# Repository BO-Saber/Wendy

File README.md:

# Wendy
---
I build a powerful WiFi Analyzer Toolkit using Wemos D1 Mini (ESP8266) to scan nearby networks, This DIY project is perfect for Arduino lovers, robotics enthusiasts, and anyone interested in network tools and wireless optimization.

---
# Design

# Circuit Diagram 

# quartzcomponents.com Cart

# Zbotic Cart

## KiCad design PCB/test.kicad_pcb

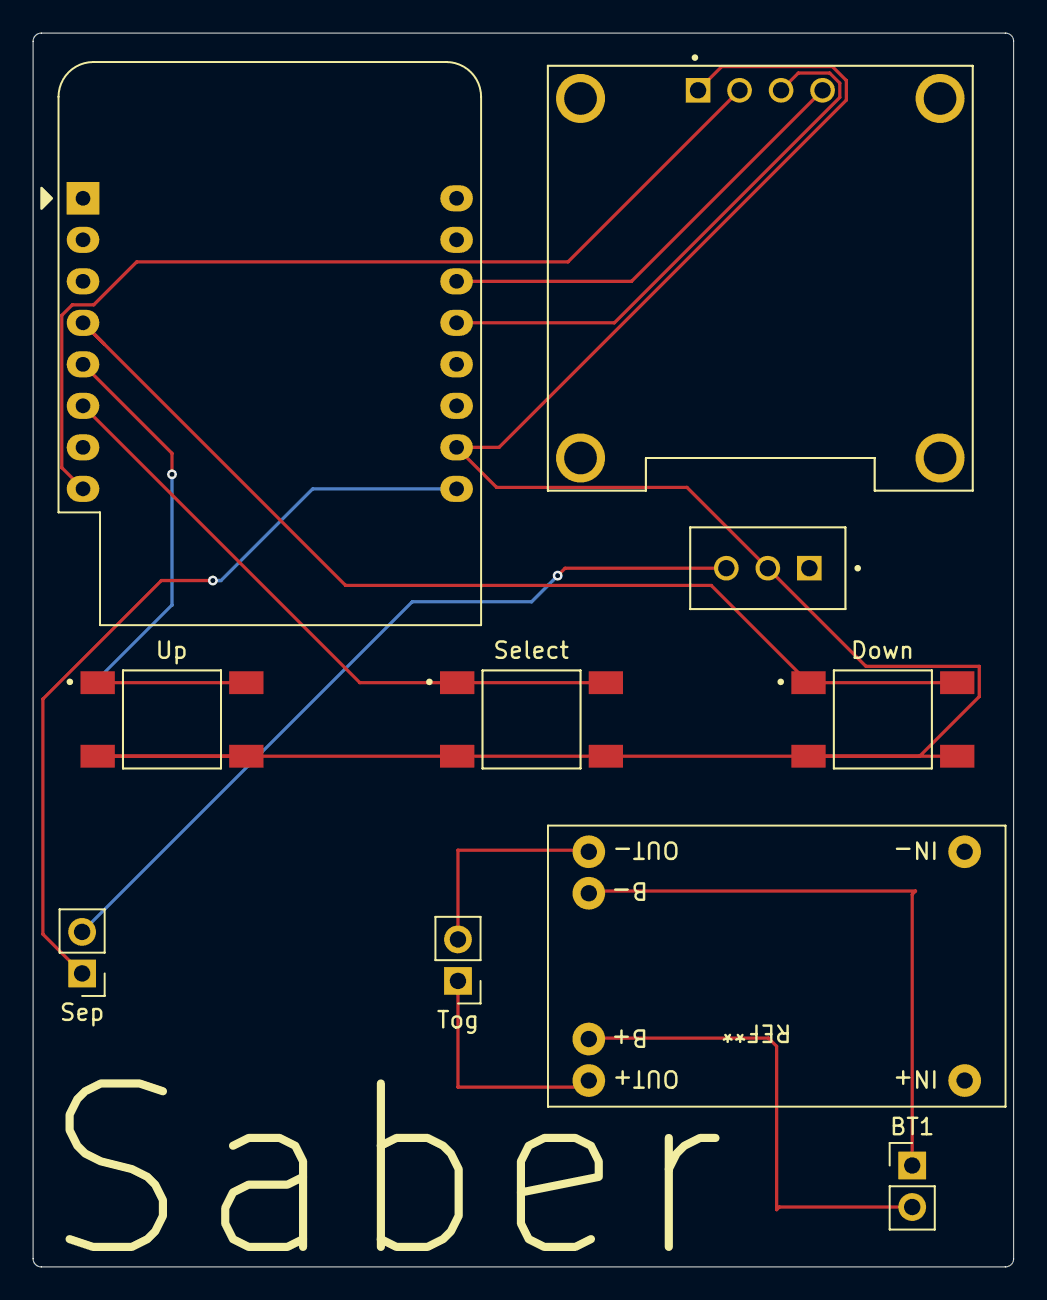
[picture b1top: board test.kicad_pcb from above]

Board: 2 copper layers, 60.0 x 75.5 mm, 9 parts (0 on the bottom side), 9 nets.

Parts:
BT1: Battery_Cell; PinHeader_1x02_P2.54mm_Vertical
Down: Down; SW_4-1437565-2
S1: ATE1D-2M3-10-Z; SW_ATE1D-2M3-10-Z
Select: Select; SW_4-1437565-2
Sep: Conn_01x02_Pin; PinHeader_1x02_P2.54mm_Vertical
Tog: Conn_01x02_Pin; PinHeader_1x02_P2.54mm_Vertical
U1: WEMOS_D1_mini; WEMOS_D1_mini_light
U3: DM-OLED096-636; MODULE_DM-OLED096-636
Up: Up; SW_4-1437565-2

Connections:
unnamed: Sep.1, U1.9 (5V)
unnamed: S1.3, Sep.2
unnamed: U1.8 (3V3), U3.2 (VCC_IN)
unnamed: Down.3, Down.4, S1.2, Select.3, Select.4, U1.10 (GND), U3.1 (GND), Up.3, Up.4
unnamed: U1.5 (MISO/D6), Up.1, Up.2
unnamed: Select.1, Select.2, U1.6 (MOSI/D7)
unnamed: Down.1, Down.2, U1.4 (SCK/D5)
unnamed: U1.14 (SCL/D1), U3.4 (SDA)
unnamed: U1.13 (SDA/D2), U3.3 (SCL)

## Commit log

2026-05-10 Create m
2026-05-10 Rename PCB/m to PCB/test-backups/m
2026-05-10 Rename ARM-ANDO-bom.csv to bom.csv
